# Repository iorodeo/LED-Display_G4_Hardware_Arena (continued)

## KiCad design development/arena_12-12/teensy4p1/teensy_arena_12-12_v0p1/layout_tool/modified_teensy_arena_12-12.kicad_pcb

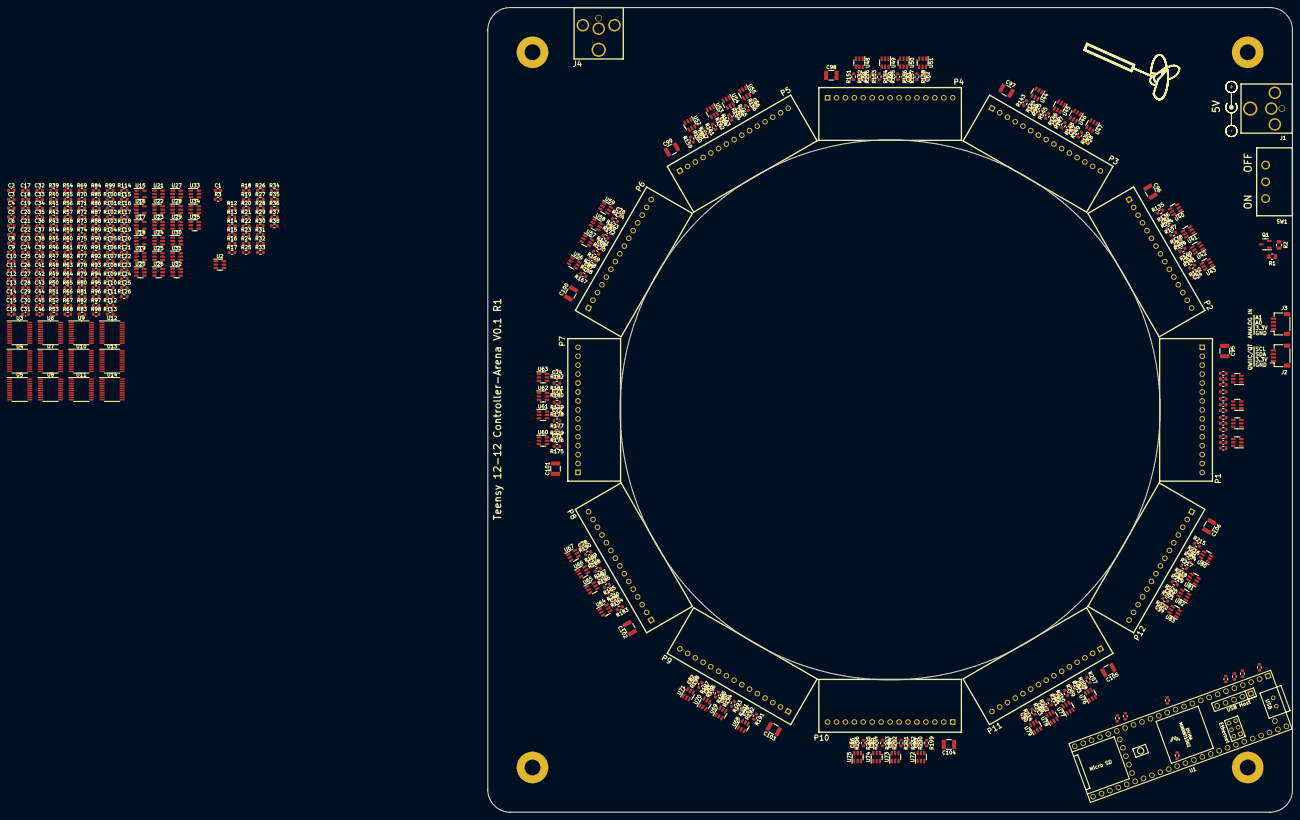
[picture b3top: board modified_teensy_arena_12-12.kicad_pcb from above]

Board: 6 copper layers, 228.6 x 228.6 mm, 445 parts (0 on the bottom side), 504 nets, no tracks yet.

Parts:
C1, C2, C3, C4, C5, C6, C7, C8, C9, C10, C11, C12, C13, C14, C15, C16, C17, C18, C19, C20, C21, C22, C23, C24, C25, C26, C27, C28, C29, C30, C31, C32, C33, C34, C35, C36, C37, C38, C39, C40, C41, C42, C43, C44, C45, C46, C47, C48, C49, C50, C51, C52, C53, C54, C55, C56, C57, C58, C59, C60, C61, C62, C63, C64, C65, C66, C67, C68, C69, C70, C71, C72, C73, C74, C75, C76, C77, C78, C79, C80, C81, C82, C83, C84, C85, C86, C87, C88, C89, C90, C91, C92, C93, C94: 0.1uF; C_0603_1608Metric
C95, C96, C97, C98, C99, C100, C101, C102, C103, C104, C105, C106: 100uF; C_1210_3225Metric
H1, H2, H3, H4: MountingHole_Pad; MountingHole_4.5mm_Pad
J1, J4: Barrel_Jack; DCJACK_2PIN_HIGHCURRENT
J2, J3: Conn_01x04; JST_SH_SM04B-SRSS-TB_1x04-1MP_P1.00mm_Horizontal
P1, P2, P3, P4, P5, P6, P7, P8, P9, P10, P11, P12: CONN15; HEADER_TOP
Q1: MOSFET_NCHAN; SOT-23-3
R1: 200; R_0805_2012Metric
R2: 20k; R_0805_2012Metric
R3, R4, R5, R6, R7, R8, R9, R10, R11, R12, R13, R14, R15, R16, R17, R18, R19, R20, R21, R22, R23, R24, R25, R26, R27, R28, R29, R30, R31, R32, R33, R34, R35, R36, R37, R38, R39, R40, R41, R42, R43, R44, R45, R46, R47, R48, R49, R50, R51, R52, R53, R54, R55, R56, R57, R58, R59, R60, R61, R62, R63, R64, R65, R66, R67, R68, R69, R70, R71, R72, R73, R74, R75, R76, R77, R78, R79, R80, R81, R82, R83, R84, R85, R86, R87, R88, R89, R90, R91, R92, R93, R94, R95, R96, R97, R98, R99, R100, R101, R102, R103, R104, R105, R106, R107, R108, R109, R110, R111, R112, R113, R114, R115, R116, R117, R118, R119, R120, R121, R122, R123, R124, R125, R126, R127, R128, R129, R130, R131, R132, R133, R134, R135, R136, R137, R138, R139, R140, R141, R142, R143, R144, R145, R146, R147, R148, R149, R150, R151, R152, R153, R154, R155, R156, R157, R158, R159, R160, R161, R162, R163, R164, R165, R166, R167, R168, R169, R170, R171, R172, R173, R174, R175, R176, R177, R178, R179, R180, R181, R182, R183, R184, R185, R186, R187, R188, R189, R190, R191, R192, R193, R194, R195, R196, R197, R198, R199, R200, R201, R202, R203, R204, R205, R206, R207, R208, R209, R210, R211, R212, R213, R214, R215, R216, R217, R218, R219, R220, R221, R222, R223, R224, R225, R226, R227, R228, R229, R230, R231, R232, R233, R234: 68; R_0603_1608Metric
SW1: SW_SPDT; slide_switch
U1: Teensy4.1; Teensy41
U2, U19, U20, U21, U22, U23, U24, U25, U26, U27, U28, U29, U30, U31, U32, U33, U34, U35, U36, U37, U38, U39, U40, U41, U42, U43, U44, U45, U46, U47, U48, U49, U50, U51, U52, U53, U54, U55, U56, U57, U58, U59, U60, U61, U62, U63, U64, U65, U66, U67, U68, U69, U70, U71, U72, U73, U74, U75, U76, U77, U78, U79, U80, U81, U82, U83: 74LVC2G17; SOT-23-6
U3, U4, U5, U6, U7, U8, U9, U10, U11, U12, U13, U14: TXB0108PW; TSSOP-20_4.4x6.5mm_P0.65mm
U15, U16, U17, U18: 74LVC1G17; SOT-23-5

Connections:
+3.3V: C1.1, C2.1, C4.1, C6.1, C8.1, C10.1, C12.1, C14.1, C16.1, C18.1, C20.1, C22.1, C24.1, C26.1, C27.1, C28.1, C29.1, C30.1, C31.1, C32.1, C33.1, C34.1, C35.1, C36.1, C37.1, C38.1, C39.1, C40.1, C41.1, C42.1, C43.1, C44.1, C45.1, C46.1, C47.1, C48.1, C49.1, C50.1, C51.1, C52.1, C53.1, C54.1, C55.1, C56.1, C57.1, C58.1, C59.1, C60.1, C61.1, C62.1, C63.1, C64.1, C65.1, C66.1, C67.1, C68.1, C69.1, C70.1, C71.1, C72.1, C73.1, C74.1, C75.1, C76.1, C77.1, C78.1, C79.1, C80.1, C81.1, C82.1, C83.1, C84.1, C85.1, C86.1, C87.1, C88.1, C89.1, C90.1, C91.1, C92.1, C93.1, C94.1, J2.2, J3.2, U1.15 (3V3), U1.46 (3V3), U2.5 (VCC), U3.2 (VCCA), U3.10 (OE), U4.2 (VCCA), U4.10 (OE), U5.2 (VCCA), U5.10 (OE), U6.2 (VCCA), U6.10 (OE), U7.2 (VCCA), U7.10 (OE), U8.2 (VCCA), U8.10 (OE), U9.2 (VCCA), U9.10 (OE), U10.2 (VCCA), U10.10 (OE), U11.2 (VCCA), U11.10 (OE), U12.2 (VCCA), U12.10 (OE), U13.2 (VCCA), U13.10 (OE), U14.2 (VCCA), U14.10 (OE), U15.5 (VCC), U16.5 (VCC), U17.5 (VCC), U18.5 (VCC), U19.5 (VCC), U20.5 (VCC), U21.5 (VCC), U22.5 (VCC), U23.5 (VCC), U24.5 (VCC), U25.5 (VCC), U26.5 (VCC), U27.5 (VCC), U28.5 (VCC), U29.5 (VCC), U30.5 (VCC), U31.5 (VCC), U32.5 (VCC), U33.5 (VCC), U34.5 (VCC), U35.5 (VCC), U36.5 (VCC), U37.5 (VCC), U38.5 (VCC), U39.5 (VCC), U40.5 (VCC), U41.5 (VCC), U42.5 (VCC), U43.5 (VCC), U44.5 (VCC), U45.5 (VCC), U46.5 (VCC), U47.5 (VCC), U48.5 (VCC), U49.5 (VCC), U50.5 (VCC), U51.5 (VCC), U52.5 (VCC), U53.5 (VCC), U54.5 (VCC), U55.5 (VCC), U56.5 (VCC), U57.5 (VCC), U58.5 (VCC), U59.5 (VCC), U60.5 (VCC), U61.5 (VCC), U62.5 (VCC), U63.5 (VCC), U64.5 (VCC), U65.5 (VCC), U66.5 (VCC), U67.5 (VCC), U68.5 (VCC), U69.5 (VCC), U70.5 (VCC), U71.5 (VCC), U72.5 (VCC), U73.5 (VCC), U74.5 (VCC), U75.5 (VCC), U76.5 (VCC), U77.5 (VCC), U78.5 (VCC), U79.5 (VCC), U80.5 (VCC), U81.5 (VCC), U82.5 (VCC), U83.5 (VCC)
+5V: C3.1, C5.1, C7.1, C9.1, C11.1, C13.1, C15.1, C17.1, C19.1, C21.1, C23.1, C25.1, C95.1, C96.1, C97.1, C98.1, C99.1, C100.1, C101.1, C102.1, C103.1, C104.1, C105.1, C106.1, J4.1, P1.1, P2.1, P3.1, P4.1, P5.1, P6.1, P7.1, P8.1, P9.1, P10.1, P11.1, P12.1, SW1.2 (B), U3.19 (VCCB), U4.19 (VCCB), U5.19 (VCCB), U6.19 (VCCB), U7.19 (VCCB), U8.19 (VCCB), U9.19 (VCCB), U10.19 (VCCB), U11.19 (VCCB), U12.19 (VCCB), U13.19 (VCCB), U14.19 (VCCB)
/Level Shifters/PAN3V.CS_00: R8.2, U19.1
/Level Shifters/PAN3V.CS_01: R9.2, U19.3
/Level Shifters/PAN3V.CS_02: R10.2, U20.1
/Level Shifters/PAN3V.CS_03: R11.2, U20.3
/Level Shifters/PAN3V.CS_04: R12.2, U21.1
/Level Shifters/PAN3V.CS_05: R13.2, U21.3
/Level Shifters/PAN3V.CS_06: R14.2, U22.1
/Level Shifters/PAN3V.CS_07: R15.2, U22.3
/Level Shifters/PAN3V.CS_08: R16.2, U23.1
/Level Shifters/PAN3V.CS_09: R17.2, U23.3
/Level Shifters/PAN3V.CS_10: R18.2, U24.1
/Level Shifters/PAN3V.CS_11: R19.2, U24.3
/Level Shifters/PAN3V.CS_12: R20.2, U25.1
/Level Shifters/PAN3V.CS_13: R21.2, U25.3
/Level Shifters/PAN3V.CS_14: R22.2, U26.1
/Level Shifters/PAN3V.CS_15: R23.2, U26.3
/Level Shifters/PAN3V.CS_16: R24.2, U27.1
/Level Shifters/PAN3V.CS_17: R25.2, U27.3
/Level Shifters/PAN3V.CS_18: R26.2, U28.1
/Level Shifters/PAN3V.CS_19: R27.2, U28.3
/Level Shifters/PAN3V.CS_20: R28.2, U29.1
/Level Shifters/PAN3V.CS_21: R29.2, U29.3
/Level Shifters/PAN3V.CS_22: R30.2, U30.1
/Level Shifters/PAN3V.CS_23: R31.2, U30.3
/Level Shifters/PAN3V.CS_24: R32.2, U31.1
/Level Shifters/PAN3V.CS_25: R33.2, U31.3
/Level Shifters/PAN3V.CS_26: R34.2, U32.1
/Level Shifters/PAN3V.CS_27: R35.2, U32.3
/Level Shifters/PAN3V.CS_28: R36.2, U33.1
/Level Shifters/PAN3V.CS_29: R37.2, U33.3
/Level Shifters/PAN3V.EXT_INT: R38.2, U34.3
/Level Shifters/PAN3V.MISO_0: R125.1, U2.1
/Level Shifters/PAN3V.MISO_1: R126.1, U2.3
/Level Shifters/PAN3V.MOSI_0: R5.2, U16.2
/Level Shifters/PAN3V.MOSI_1: R7.2, U18.2
/Level Shifters/PAN3V.RESET: R3.2, U34.1
/Level Shifters/PAN3V.SCK_0: R4.2, U15.2
/Level Shifters/PAN3V.SCK_1: R6.2, U17.2
/Level Shifters/PAN5V.CS_00_P1: R69.1, U37.3
/Level Shifters/PAN5V.CS_00_P7: R63.1, U61.3
/Level Shifters/PAN5V.CS_01_P1: R64.1, U37.1
/Level Shifters/PAN5V.CS_01_P7: R65.1, U61.1
/Level Shifters/PAN5V.CS_02_P1: R66.1, U38.3
/Level Shifters/PAN5V.CS_02_P7: R67.1, U62.3
/Level Shifters/PAN5V.CS_03_P1: R68.1, U38.1
/Level Shifters/PAN5V.CS_03_P7: R70.1, U62.1
/Level Shifters/PAN5V.CS_04_P1: R71.1, U39.3
/Level Shifters/PAN5V.CS_04_P7: R72.1, U63.3
/Level Shifters/PAN5V.CS_05_P2: R73.1, U41.3
/Level Shifters/PAN5V.CS_05_P8: R74.1, U65.3
/Level Shifters/PAN5V.CS_06_P2: R75.1, U41.1
/Level Shifters/PAN5V.CS_06_P8: R76.1, U65.1
/Level Shifters/PAN5V.CS_07_P2: R77.1, U42.3
/Level Shifters/PAN5V.CS_07_P8: R78.1, U66.3
/Level Shifters/PAN5V.CS_08_P2: R79.1, U42.1
/Level Shifters/PAN5V.CS_08_P8: R80.1, U66.1
/Level Shifters/PAN5V.CS_09_P2: R81.1, U43.3
/Level Shifters/PAN5V.CS_09_P8: R82.1, U67.3
/Level Shifters/PAN5V.CS_10_P3: R83.1, U45.3
/Level Shifters/PAN5V.CS_10_P9: R84.1, U69.3
/Level Shifters/PAN5V.CS_11_P3: R85.1, U45.1
/Level Shifters/PAN5V.CS_11_P9: R86.1, U69.1
/Level Shifters/PAN5V.CS_12_P3: R87.1, U46.3
/Level Shifters/PAN5V.CS_12_P9: R88.1, U70.3
/Level Shifters/PAN5V.CS_13_P3: R89.1, U46.1
/Level Shifters/PAN5V.CS_13_P9: R90.1, U70.1
/Level Shifters/PAN5V.CS_14_P3: R91.1, U47.3
/Level Shifters/PAN5V.CS_14_P9: R92.1, U71.3
/Level Shifters/PAN5V.CS_15_P4: R93.1, U49.3
/Level Shifters/PAN5V.CS_15_P10: R94.1, U73.3
/Level Shifters/PAN5V.CS_16_P4: R95.1, U49.1
/Level Shifters/PAN5V.CS_16_P10: R96.1, U73.1
/Level Shifters/PAN5V.CS_17_P4: R97.1, U50.3
/Level Shifters/PAN5V.CS_17_P10: R98.1, U74.3
/Level Shifters/PAN5V.CS_18_P4: R99.1, U50.1
/Level Shifters/PAN5V.CS_18_P10: R100.1, U74.1
/Level Shifters/PAN5V.CS_19_P4: R101.1, U51.3
/Level Shifters/PAN5V.CS_19_P10: R102.1, U75.3
/Level Shifters/PAN5V.CS_20_P5: R103.1, U53.3
/Level Shifters/PAN5V.CS_20_P11: R104.1, U77.3
/Level Shifters/PAN5V.CS_21_P5: R105.1, U53.1
/Level Shifters/PAN5V.CS_21_P11: R106.1, U77.1
/Level Shifters/PAN5V.CS_22_P5: R107.1, U54.3
/Level Shifters/PAN5V.CS_22_P11: R108.1, U78.3
/Level Shifters/PAN5V.CS_23_P5: R109.1, U54.1
/Level Shifters/PAN5V.CS_23_P11: R110.1, U78.1
/Level Shifters/PAN5V.CS_24_P5: R111.1, U55.3
/Level Shifters/PAN5V.CS_24_P11: R112.1, U79.3
/Level Shifters/PAN5V.CS_25_P6: R113.1, U57.3
/Level Shifters/PAN5V.CS_25_P12: R114.1, U81.3
/Level Shifters/PAN5V.CS_26_P6: R115.1, U57.1
/Level Shifters/PAN5V.CS_26_P12: R116.1, U81.1
/Level Shifters/PAN5V.CS_27_P6: R117.1, U58.3
/Level Shifters/PAN5V.CS_27_P12: R118.1, U82.3
/Level Shifters/PAN5V.CS_28_P6: R119.1, U58.1
/Level Shifters/PAN5V.CS_28_P12: R120.1, U82.1
/Level Shifters/PAN5V.CS_29_P6: R121.1, U59.3
/Level Shifters/PAN5V.CS_29_P12: R122.1, U83.3
/Level Shifters/PAN5V.EXT_INT: R124.1, U39.1, U43.1, U47.1, U51.1, U55.1, U59.1, U63.1, U67.1, U71.1, U75.1, U79.1, U83.1
/Level Shifters/PAN5V.MISO_0: R223.2, R224.2, R225.2, R226.2, R227.2, R228.2, U35.1
/Level Shifters/PAN5V.MISO_1: R229.2, R230.2, R231.2, R232.2, R233.2, R234.2, U35.3
/Level Shifters/PAN5V.MOSI_0_P1: R45.1, U36.1
/Level Shifters/PAN5V.MOSI_0_P2: R46.1, U40.1
/Level Shifters/PAN5V.MOSI_0_P3: R47.1, U44.1
/Level Shifters/PAN5V.MOSI_0_P4: R48.1, U48.1
/Level Shifters/PAN5V.MOSI_0_P5: R49.1, U52.1
/Level Shifters/PAN5V.MOSI_0_P6: R50.1, U56.1
/Level Shifters/PAN5V.MOSI_1_P7: R57.1, U60.1
/Level Shifters/PAN5V.MOSI_1_P8: R58.1, U64.1
/Level Shifters/PAN5V.MOSI_1_P9: R59.1, U68.1
/Level Shifters/PAN5V.MOSI_1_P10: R60.1, U72.1
/Level Shifters/PAN5V.MOSI_1_P11: R61.1, U76.1
/Level Shifters/PAN5V.MOSI_1_P12: R62.1, U80.1
/Level Shifters/PAN5V.RESET: R1.2, R123.1
/Level Shifters/PAN5V.SCK_0_P1: R39.1, U36.3
/Level Shifters/PAN5V.SCK_0_P2: R40.1, U40.3
/Level Shifters/PAN5V.SCK_0_P3: R41.1, U44.3
/Level Shifters/PAN5V.SCK_0_P4: R42.1, U48.3
/Level Shifters/PAN5V.SCK_0_P5: R43.1, U52.3
/Level Shifters/PAN5V.SCK_0_P6: R44.1, U56.3
/Level Shifters/PAN5V.SCK_1_P7: R51.1, U60.3
/Level Shifters/PAN5V.SCK_1_P8: R52.1, U64.3
/Level Shifters/PAN5V.SCK_1_P9: R53.1, U68.3
/Level Shifters/PAN5V.SCK_1_P10: R54.1, U72.3
/Level Shifters/PAN5V.SCK_1_P11: R55.1, U76.3
/Level Shifters/PAN5V.SCK_1_P12: R56.1, U80.3
/Panel Headers/HDR_CS_00_P1: P1.7, R129.1
/Panel Headers/HDR_CS_00_P7: P7.7, R177.1
/Panel Headers/HDR_CS_01_P1: P1.8, R130.1
/Panel Headers/HDR_CS_01_P7: P7.8, R178.1
/Panel Headers/HDR_CS_02_P1: P1.9, R131.1
/Panel Headers/HDR_CS_02_P7: P7.9, R179.1
/Panel Headers/HDR_CS_03_P1: P1.10, R132.1
/Panel Headers/HDR_CS_03_P7: P7.10, R180.1
/Panel Headers/HDR_CS_04_P1: P1.11, R133.1
/Panel Headers/HDR_CS_04_P7: P7.11, R181.1
/Panel Headers/HDR_CS_05_P2: P2.7, R137.1
/Panel Headers/HDR_CS_05_P8: P8.7, R185.1
/Panel Headers/HDR_CS_06_P2: P2.8, R138.1
/Panel Headers/HDR_CS_06_P8: P8.8, R186.1
/Panel Headers/HDR_CS_07_P2: P2.9, R139.1
/Panel Headers/HDR_CS_07_P8: P8.9, R187.1
/Panel Headers/HDR_CS_08_P2: P2.10, R140.1
/Panel Headers/HDR_CS_08_P8: P8.10, R188.1
/Panel Headers/HDR_CS_09_P2: P2.11, R141.1
/Panel Headers/HDR_CS_09_P8: P8.11, R189.1
/Panel Headers/HDR_CS_10_P3: P3.7, R145.1
/Panel Headers/HDR_CS_10_P9: P9.7, R193.1
/Panel Headers/HDR_CS_11_P3: P3.8, R146.1
/Panel Headers/HDR_CS_11_P9: P9.8, R194.1
/Panel Headers/HDR_CS_12_P3: P3.9, R147.1
/Panel Headers/HDR_CS_12_P9: P9.9, R195.1
/Panel Headers/HDR_CS_13_P3: P3.10, R148.1
/Panel Headers/HDR_CS_13_P9: P9.10, R196.1
/Panel Headers/HDR_CS_14_P3: P3.11, R149.1
/Panel Headers/HDR_CS_14_P9: P9.11, R197.1
/Panel Headers/HDR_CS_15_P4: P4.7, R153.1
/Panel Headers/HDR_CS_15_P10: P10.7, R201.1
/Panel Headers/HDR_CS_16_P4: P4.8, R154.1
/Panel Headers/HDR_CS_16_P10: P10.8, R202.1
/Panel Headers/HDR_CS_17_P4: P4.9, R155.1
/Panel Headers/HDR_CS_17_P10: P10.9, R203.1
/Panel Headers/HDR_CS_18_P4: P4.10, R156.1
/Panel Headers/HDR_CS_18_P10: P10.10, R204.1
/Panel Headers/HDR_CS_19_P4: P4.11, R157.1
/Panel Headers/HDR_CS_19_P10: P10.11, R205.1
/Panel Headers/HDR_CS_20_P5: P5.7, R161.1
/Panel Headers/HDR_CS_20_P11: P11.7, R209.1
/Panel Headers/HDR_CS_21_P5: P5.8, R162.1
/Panel Headers/HDR_CS_21_P11: P11.8, R210.1
/Panel Headers/HDR_CS_22_P5: P5.9, R163.1
/Panel Headers/HDR_CS_22_P11: P11.9, R211.1
/Panel Headers/HDR_CS_23_P5: P5.10, R164.1
/Panel Headers/HDR_CS_23_P11: P11.10, R212.1
/Panel Headers/HDR_CS_24_P5: P5.11, R165.1
/Panel Headers/HDR_CS_24_P11: P11.11, R213.1
/Panel Headers/HDR_CS_25_P6: P6.7, R169.1
/Panel Headers/HDR_CS_25_P12: P12.7, R217.1
/Panel Headers/HDR_CS_26_P6: P6.8, R170.1
/Panel Headers/HDR_CS_26_P12: P12.8, R218.1
/Panel Headers/HDR_CS_27_P6: P6.9, R171.1
/Panel Headers/HDR_CS_27_P12: P12.9, R219.1
/Panel Headers/HDR_CS_28_P6: P6.10, R172.1
/Panel Headers/HDR_CS_28_P12: P12.10, R220.1
/Panel Headers/HDR_CS_29_P6: P6.11, R173.1
/Panel Headers/HDR_CS_29_P12: P12.11, R221.1
/Panel Headers/HDR_EXT_INT_P1: P1.15, R134.1
/Panel Headers/HDR_EXT_INT_P2: P2.15, R142.1
/Panel Headers/HDR_EXT_INT_P3: P3.15, R150.1
/Panel Headers/HDR_EXT_INT_P4: P4.15, R158.1
/Panel Headers/HDR_EXT_INT_P5: P5.15, R166.1
/Panel Headers/HDR_EXT_INT_P6: P6.15, R174.1
/Panel Headers/HDR_EXT_INT_P7: P7.15, R182.1
/Panel Headers/HDR_EXT_INT_P8: P8.15, R190.1
/Panel Headers/HDR_EXT_INT_P9: P9.15, R198.1
/Panel Headers/HDR_EXT_INT_P10: P10.15, R206.1
/Panel Headers/HDR_EXT_INT_P11: P11.15, R214.1
/Panel Headers/HDR_EXT_INT_P12: P12.15, R222.1
/Panel Headers/HDR_MISO_0_P1: P1.6, R223.1
/Panel Headers/HDR_MISO_0_P2: P2.6, R224.1
/Panel Headers/HDR_MISO_0_P3: P3.6, R225.1
/Panel Headers/HDR_MISO_0_P4: P4.6, R226.1
/Panel Headers/HDR_MISO_0_P5: P5.6, R227.1
/Panel Headers/HDR_MISO_0_P6: P6.6, R228.1
/Panel Headers/HDR_MISO_1_P7: P7.6, R229.1
/Panel Headers/HDR_MISO_1_P8: P8.6, R230.1
/Panel Headers/HDR_MISO_1_P9: P9.6, R231.1
/Panel Headers/HDR_MISO_1_P10: P10.6, R232.1
/Panel Headers/HDR_MISO_1_P11: P11.6, R233.1
/Panel Headers/HDR_MISO_1_P12: P12.6, R234.1
/Panel Headers/HDR_MOSI_0_P1: P1.5, R128.1
/Panel Headers/HDR_MOSI_0_P2: P2.5, R136.1
/Panel Headers/HDR_MOSI_0_P3: P3.5, R144.1
/Panel Headers/HDR_MOSI_0_P4: P4.5, R152.1
/Panel Headers/HDR_MOSI_0_P5: P5.5, R160.1
/Panel Headers/HDR_MOSI_0_P6: P6.5, R168.1
/Panel Headers/HDR_MOSI_1_P7: P7.5, R176.1
/Panel Headers/HDR_MOSI_1_P8: P8.5, R184.1
/Panel Headers/HDR_MOSI_1_P9: P9.5, R192.1
/Panel Headers/HDR_MOSI_1_P10: P10.5, R200.1
/Panel Headers/HDR_MOSI_1_P11: P11.5, R208.1
/Panel Headers/HDR_MOSI_1_P12: P12.5, R216.1
/Panel Headers/HDR_RESET: P1.3, P2.3, P3.3, P4.3, P5.3, P6.3, P7.3, P8.3, P9.3, P10.3, P11.3, P12.3, Q1.3 (D)
/Panel Headers/HDR_SCK_0_P1: P1.4, R127.1
/Panel Headers/HDR_SCK_0_P2: P2.4, R135.1
/Panel Headers/HDR_SCK_0_P3: P3.4, R143.1
/Panel Headers/HDR_SCK_0_P4: P4.4, R151.1
/Panel Headers/HDR_SCK_0_P5: P5.4, R159.1
/Panel Headers/HDR_SCK_0_P6: P6.4, R167.1
/Panel Headers/HDR_SCK_1_P7: P7.4, R175.1
/Panel Headers/HDR_SCK_1_P8: P8.4, R183.1
/Panel Headers/HDR_SCK_1_P9: P9.4, R191.1
/Panel Headers/HDR_SCK_1_P10: P10.4, R199.1
/Panel Headers/HDR_SCK_1_P11: P11.4, R207.1
/Panel Headers/HDR_SCK_1_P12: P12.4, R215.1
/Power/SW_5V: J1.1, SW1.1 (A)
/Teensy/A0: J3.3, U1.36 (14_A0_TX3_SPDIF_OUT)
/Teensy/A1: J3.4, U1.37 (15_A1_RX3_SPDIF_IN)
/Teensy/SCL: J2.4, U1.41 (19_A5_SCL)
/Teensy/SDA: J2.3, U1.40 (18_A4_SDA)
/Teensy/TNY_CS_00: R8.1, U1.2 (0_RX1_CRX2_CS1)
/Teensy/TNY_CS_01: R9.1, U1.4 (2_OUT2)
/Teensy/TNY_CS_02: R10.1, U1.5 (3_LRCLK2)
/Teensy/TNY_CS_03: R11.1, U1.6 (4_BCLK2)
/Teensy/TNY_CS_04: R12.1, U1.7 (5_IN2)
/Teensy/TNY_CS_05: R13.1, U1.8 (6_OUT1D)
/Teensy/TNY_CS_06: R14.1, U1.9 (7_RX2_OUT1A)
/Teensy/TNY_CS_07: R15.1, U1.10 (8_TX2_IN1)
/Teensy/TNY_CS_08: R16.1, U1.11 (9_OUT1C)
/Teensy/TNY_CS_09: R17.1, U1.12 (10_CS_MQSR)
/Teensy/TNY_CS_10: R18.1, U1.16 (24_A10_TX6_SCL2)
/Teensy/TNY_CS_11: R19.1, U1.17 (25_A11_RX6_SDA2)
/Teensy/TNY_CS_12: R20.1, U1.20 (28_RX7)
/Teensy/TNY_CS_13: R21.1, U1.21 (29_TX7)
/Teensy/TNY_CS_14: R22.1, U1.22 (30_CRX3)
/Teensy/TNY_CS_15: R23.1, U1.23 (31_CTX3)
/Teensy/TNY_CS_16: R24.1, U1.24 (32_OUT1B)
/Teensy/TNY_CS_17: R25.1, U1.45 (23_A9_CRX1_MCLK1)
/Teensy/TNY_CS_18: R26.1, U1.44 (22_A8_CTX1)
/Teensy/TNY_CS_19: R27.1, U1.43 (21_A7_RX5_BCLK1)
/Teensy/TNY_CS_20: R28.1, U1.42 (20_A6_TX5_LRCLK1)
/Teensy/TNY_CS_21: R29.1, U1.39 (17_A3_TX4_SDA1)
/Teensy/TNY_CS_22: R30.1, U1.38 (16_A2_RX4_SCL1)
/Teensy/TNY_CS_23: R31.1, U1.33 (41_A17)
/Teensy/TNY_CS_24: R32.1, U1.32 (40_A16)
/Teensy/TNY_CS_25: R33.1, U1.31 (39_MISO1_OUT1A)
/Teensy/TNY_CS_26: R34.1, U1.30 (38_CS1_IN1)
/Teensy/TNY_CS_27: R35.1, U1.29 (37_CS)
/Teensy/TNY_CS_28: R36.1, U1.28 (36_CS)
/Teensy/TNY_CS_29: R37.1, U1.27 (35_TX8)
/Teensy/TNY_EXT_INT: R38.1, U1.25 (33_MCLK2)
/Teensy/TNY_MISO_0: U1.14 (12_MISO_MQSL), U2.6
/Teensy/TNY_MISO_1: U1.3 (1_TX1_CTX2_MISO1), U2.4
/Teensy/TNY_MOSI_0: R5.1, U1.13 (11_MOSI_CTX1)
/Teensy/TNY_MOSI_1: R7.1, U1.18 (26_A12_MOSI1)
/Teensy/TNY_RESET: R3.1, U1.26 (34_RX8)
/Teensy/TNY_SCK_0: R4.1, U1.35 (13_SCK_LED)
/Teensy/TNY_SCK_1: R6.1, U1.19 (27_A13_SCK1)
GND: C1.2, C2.2, C3.2, C4.2, C5.2, C6.2, C7.2, C8.2, C9.2, C10.2, C11.2, C12.2, C13.2, C14.2, C15.2, C16.2, C17.2, C18.2, C19.2, C20.2, C21.2, C22.2, C23.2, C24.2, C25.2, C26.2, C27.2, C28.2, C29.2, C30.2, C31.2, C32.2, C33.2, C34.2, C35.2, C36.2, C37.2, C38.2, C39.2, C40.2, C41.2, C42.2, C43.2, C44.2, C45.2, C46.2, C47.2, C48.2, C49.2, C50.2, C51.2, C52.2, C53.2, C54.2, C55.2, C56.2, C57.2, C58.2, C59.2, C60.2, C61.2, C62.2, C63.2, C64.2, C65.2, C66.2, C67.2, C68.2, C69.2, C70.2, C71.2, C72.2, C73.2, C74.2, C75.2, C76.2, C77.2, C78.2, C79.2, C80.2, C81.2, C82.2, C83.2, C84.2, C85.2, C86.2, C87.2, C88.2, C89.2, C90.2, C91.2, C92.2, C93.2, C94.2, C95.2, C96.2, C97.2, C98.2, C99.2, C100.2, C101.2, C102.2, C103.2, C104.2, C105.2, C106.2, H1.1, H2.1, H3.1, H4.1, J1.2, J2.1, J3.1, J4.2, P1.2, P2.2, P3.2, P4.2, P5.2, P6.2, P7.2, P8.2, P9.2, P10.2, P11.2, P12.2, Q1.2 (S), R2.1, SW1.3 (C), U1.1 (GND), U1.34 (GND), U1.47 (GND), U2.2 (GND), U3.11 (GND), U4.11 (GND), U5.11 (GND), U6.11 (GND), U7.11 (GND), U8.11 (GND), U9.11 (GND), U10.11 (GND), U11.11 (GND), U12.11 (GND), U13.11 (GND), U14.11 (GND), U15.3 (GND), U16.3 (GND), U17.3 (GND), U18.3 (GND), U19.2 (GND), U20.2 (GND), U21.2 (GND), U22.2 (GND), U23.2 (GND), U24.2 (GND), U25.2 (GND), U26.2 (GND), U27.2 (GND), U28.2 (GND), U29.2 (GND), U30.2 (GND), U31.2 (GND), U32.2 (GND), U33.2 (GND), U34.2 (GND), U35.2 (GND), U36.2 (GND), U37.2 (GND), U38.2 (GND), U39.2 (GND), U40.2 (GND), U41.2 (GND), U42.2 (GND), U43.2 (GND), U44.2 (GND), U45.2 (GND), U46.2 (GND), U47.2 (GND), U48.2 (GND), U49.2 (GND), U50.2 (GND), U51.2 (GND), U52.2 (GND), U53.2 (GND), U54.2 (GND), U55.2 (GND), U56.2 (GND), U57.2 (GND), U58.2 (GND), U59.2 (GND), U60.2 (GND), U61.2 (GND), U62.2 (GND), U63.2 (GND), U64.2 (GND), U65.2 (GND), U66.2 (GND), U67.2 (GND), U68.2 (GND), U69.2 (GND), U70.2 (GND), U71.2 (GND), U72.2 (GND), U73.2 (GND), U74.2 (GND), U75.2 (GND), U76.2 (GND), U77.2 (GND), U78.2 (GND), U79.2 (GND), U80.2 (GND), U81.2 (GND), U82.2 (GND), U83.2 (GND)
unnamed: Q1.1 (G), R1.1, R2.2
unnamed: R127.2, U36.4
unnamed: R128.2, U36.6
unnamed: R129.2, U37.4
unnamed: R130.2, U37.6
unnamed: R131.2, U38.4
unnamed: R132.2, U38.6
unnamed: R133.2, U39.4
unnamed: R134.2, U39.6
unnamed: R135.2, U40.4
unnamed: R136.2, U40.6
unnamed: R137.2, U41.4
unnamed: R138.2, U41.6
unnamed: R139.2, U42.4
unnamed: R140.2, U42.6
unnamed: R141.2, U43.4
unnamed: R142.2, U43.6
unnamed: R143.2, U44.4
unnamed: R144.2, U44.6
unnamed: R145.2, U45.4
unnamed: R146.2, U45.6
unnamed: R147.2, U46.4
unnamed: R148.2, U46.6
unnamed: R149.2, U47.4
unnamed: R150.2, U47.6
unnamed: R151.2, U48.4
unnamed: R152.2, U48.6
unnamed: R153.2, U49.4
unnamed: R154.2, U49.6
unnamed: R155.2, U50.4
unnamed: R156.2, U50.6
unnamed: R157.2, U51.4
unnamed: R158.2, U51.6
unnamed: R159.2, U52.4
unnamed: R160.2, U52.6
unnamed: R161.2, U53.4
unnamed: R162.2, U53.6
unnamed: R163.2, U54.4
unnamed: R164.2, U54.6
unnamed: R165.2, U55.4
unnamed: R166.2, U55.6
unnamed: R167.2, U56.4
unnamed: R168.2, U56.6
unnamed: R169.2, U57.4
unnamed: R170.2, U57.6
unnamed: R171.2, U58.4
unnamed: R172.2, U58.6
unnamed: R173.2, U59.4
unnamed: R174.2, U59.6
unnamed: R175.2, U60.4
unnamed: R176.2, U60.6
unnamed: R177.2, U61.4
unnamed: R178.2, U61.6
unnamed: R179.2, U62.4
unnamed: R180.2, U62.6
unnamed: R181.2, U63.4
unnamed: R182.2, U63.6
unnamed: R183.2, U64.4
unnamed: R184.2, U64.6
unnamed: R185.2, U65.4
unnamed: R186.2, U65.6
unnamed: R187.2, U66.4
unnamed: R188.2, U66.6
unnamed: R189.2, U67.4
unnamed: R190.2, U67.6
unnamed: R191.2, U68.4
unnamed: R192.2, U68.6
unnamed: R193.2, U69.4
unnamed: R194.2, U69.6
unnamed: R195.2, U70.4
unnamed: R196.2, U70.6
unnamed: R197.2, U71.4
unnamed: R198.2, U71.6
unnamed: R199.2, U72.4
unnamed: R200.2, U72.6
unnamed: R201.2, U73.4
unnamed: R202.2, U73.6
unnamed: R203.2, U74.4
unnamed: R204.2, U74.6
unnamed: R205.2, U75.4
unnamed: R206.2, U75.6
unnamed: R207.2, U76.4
unnamed: R208.2, U76.6
unnamed: R209.2, U77.4
unnamed: R210.2, U77.6
unnamed: R211.2, U78.4
unnamed: R212.2, U78.6
unnamed: R213.2, U79.4
unnamed: R214.2, U79.6
unnamed: R215.2, U80.4
unnamed: R216.2, U80.6
unnamed: R217.2, U81.4
unnamed: R218.2, U81.6
unnamed: R219.2, U82.4
unnamed: R220.2, U82.6
unnamed: R221.2, U83.4
unnamed: R222.2, U83.6
unnamed: U3.1 (A1), U3.3 (A2), U3.5 (A4), U3.7 (A6), U3.8 (A7), U3.9 (A8), U15.4
unnamed: R39.2, U3.20 (B1)
unnamed: R40.2, U3.18 (B2)
unnamed: R41.2, U3.16 (B4)
unnamed: R42.2, U3.14 (B6)
unnamed: R43.2, U3.13 (B7)
unnamed: R44.2, U3.12 (B8)
unnamed: U4.1 (A1), U4.3 (A2), U4.5 (A4), U4.7 (A6), U4.8 (A7), U4.9 (A8), U16.4
unnamed: R45.2, U4.20 (B1)
unnamed: R46.2, U4.18 (B2)
unnamed: R47.2, U4.16 (B4)
unnamed: R48.2, U4.14 (B6)
unnamed: R49.2, U4.13 (B7)
unnamed: R50.2, U4.12 (B8)
unnamed: U5.1 (A1), U5.3 (A2), U5.5 (A4), U5.7 (A6), U5.8 (A7), U5.9 (A8), U17.4
unnamed: R51.2, U5.20 (B1)
unnamed: R52.2, U5.18 (B2)
unnamed: R53.2, U5.16 (B4)
unnamed: R54.2, U5.14 (B6)
unnamed: R55.2, U5.13 (B7)
unnamed: R56.2, U5.12 (B8)
unnamed: U6.1 (A1), U6.3 (A2), U6.5 (A4), U6.7 (A6), U6.8 (A7), U6.9 (A8), U18.4
unnamed: R57.2, U6.20 (B1)
unnamed: R58.2, U6.18 (B2)
unnamed: R59.2, U6.16 (B4)
unnamed: R60.2, U6.14 (B6)
unnamed: R61.2, U6.13 (B7)
unnamed: R62.2, U6.12 (B8)
unnamed: U7.1 (A1), U7.3 (A2), U19.6
unnamed: U7.4 (A3), U7.5 (A4), U19.4
unnamed: U7.6 (A5), U7.7 (A6), U20.6
unnamed: U7.8 (A7), U7.9 (A8), U20.4
unnamed: R69.2, U7.20 (B1)
unnamed: R63.2, U7.18 (B2)
unnamed: R64.2, U7.17 (B3)
unnamed: R65.2, U7.16 (B4)
unnamed: R66.2, U7.15 (B5)
unnamed: R67.2, U7.14 (B6)
unnamed: R68.2, U7.13 (B7)
unnamed: R70.2, U7.12 (B8)
unnamed: U8.1 (A1), U8.3 (A2), U21.6
unnamed: U8.4 (A3), U8.5 (A4), U21.4
unnamed: U8.6 (A5), U8.7 (A6), U22.6
unnamed: U8.8 (A7), U8.9 (A8), U22.4
unnamed: R71.2, U8.20 (B1)
unnamed: R72.2, U8.18 (B2)
unnamed: R73.2, U8.17 (B3)
unnamed: R74.2, U8.16 (B4)
unnamed: R75.2, U8.15 (B5)
unnamed: R76.2, U8.14 (B6)
unnamed: R77.2, U8.13 (B7)
unnamed: R78.2, U8.12 (B8)
unnamed: U9.1 (A1), U9.3 (A2), U23.6
unnamed: U9.4 (A3), U9.5 (A4), U23.4
unnamed: U9.6 (A5), U9.7 (A6), U24.6
unnamed: U9.8 (A7), U9.9 (A8), U24.4
unnamed: R79.2, U9.20 (B1)
unnamed: R80.2, U9.18 (B2)
unnamed: R81.2, U9.17 (B3)
unnamed: R82.2, U9.16 (B4)
unnamed: R83.2, U9.15 (B5)
unnamed: R84.2, U9.14 (B6)
unnamed: R85.2, U9.13 (B7)
unnamed: R86.2, U9.12 (B8)
unnamed: U10.1 (A1), U10.3 (A2), U25.6
unnamed: U10.4 (A3), U10.5 (A4), U25.4
unnamed: U10.6 (A5), U10.7 (A6), U26.6
unnamed: U10.8 (A7), U10.9 (A8), U26.4
unnamed: R87.2, U10.20 (B1)
unnamed: R88.2, U10.18 (B2)
unnamed: R89.2, U10.17 (B3)
unnamed: R90.2, U10.16 (B4)
unnamed: R91.2, U10.15 (B5)
unnamed: R92.2, U10.14 (B6)
unnamed: R93.2, U10.13 (B7)
unnamed: R94.2, U10.12 (B8)
unnamed: U11.1 (A1), U11.3 (A2), U27.6
unnamed: U11.4 (A3), U11.5 (A4), U27.4
unnamed: U11.6 (A5), U11.7 (A6), U28.6
unnamed: U11.8 (A7), U11.9 (A8), U28.4
unnamed: R95.2, U11.20 (B1)
unnamed: R96.2, U11.18 (B2)
unnamed: R97.2, U11.17 (B3)
unnamed: R98.2, U11.16 (B4)
unnamed: R99.2, U11.15 (B5)
unnamed: R100.2, U11.14 (B6)
unnamed: R101.2, U11.13 (B7)
unnamed: R102.2, U11.12 (B8)
unnamed: U12.1 (A1), U12.3 (A2), U29.6
unnamed: U12.4 (A3), U12.5 (A4), U29.4
unnamed: U12.6 (A5), U12.7 (A6), U30.6
unnamed: U12.8 (A7), U12.9 (A8), U30.4
unnamed: R103.2, U12.20 (B1)
unnamed: R104.2, U12.18 (B2)
unnamed: R105.2, U12.17 (B3)
unnamed: R106.2, U12.16 (B4)
unnamed: R107.2, U12.15 (B5)
unnamed: R108.2, U12.14 (B6)
unnamed: R109.2, U12.13 (B7)
unnamed: R110.2, U12.12 (B8)
unnamed: U13.1 (A1), U13.3 (A2), U31.6
unnamed: U13.4 (A3), U13.5 (A4), U31.4
unnamed: U13.6 (A5), U13.7 (A6), U32.6
unnamed: U13.8 (A7), U13.9 (A8), U32.4
unnamed: R111.2, U13.20 (B1)
unnamed: R112.2, U13.18 (B2)
unnamed: R113.2, U13.17 (B3)
unnamed: R114.2, U13.16 (B4)
unnamed: R115.2, U13.15 (B5)
unnamed: R116.2, U13.14 (B6)
unnamed: R117.2, U13.13 (B7)
unnamed: R118.2, U13.12 (B8)
unnamed: U14.1 (A1), U14.3 (A2), U33.6
unnamed: U14.4 (A3), U14.5 (A4), U33.4
unnamed: U14.6 (A5), U34.6
unnamed: U14.7 (A6), U34.4
unnamed: R125.2, U14.8 (A7)
unnamed: R126.2, U14.9 (A8)
unnamed: R119.2, U14.20 (B1)
unnamed: R120.2, U14.18 (B2)
unnamed: R121.2, U14.17 (B3)
unnamed: R122.2, U14.16 (B4)
unnamed: R123.2, U14.15 (B5)
unnamed: R124.2, U14.14 (B6)
unnamed: U14.13 (B7), U35.6
unnamed: U14.12 (B8), U35.4
